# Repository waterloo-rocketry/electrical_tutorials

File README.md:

# electrical_tutorials
Hardware &amp; software used in electrical tutorials

Contents:
* pic_template.X: contains an empty MPLAB X project for use with the `picdev` board (see schematics in canhw). The project is set up with all the necessary files to get CAN communication up and running.
* 2019_PIC_CAN_dev_board: contains the reference schematics used in the 2019 electrical Kicad tutorials.
* 2020_keychain_PIC: contains the desing files for the 2020 KiCAD tutorials.

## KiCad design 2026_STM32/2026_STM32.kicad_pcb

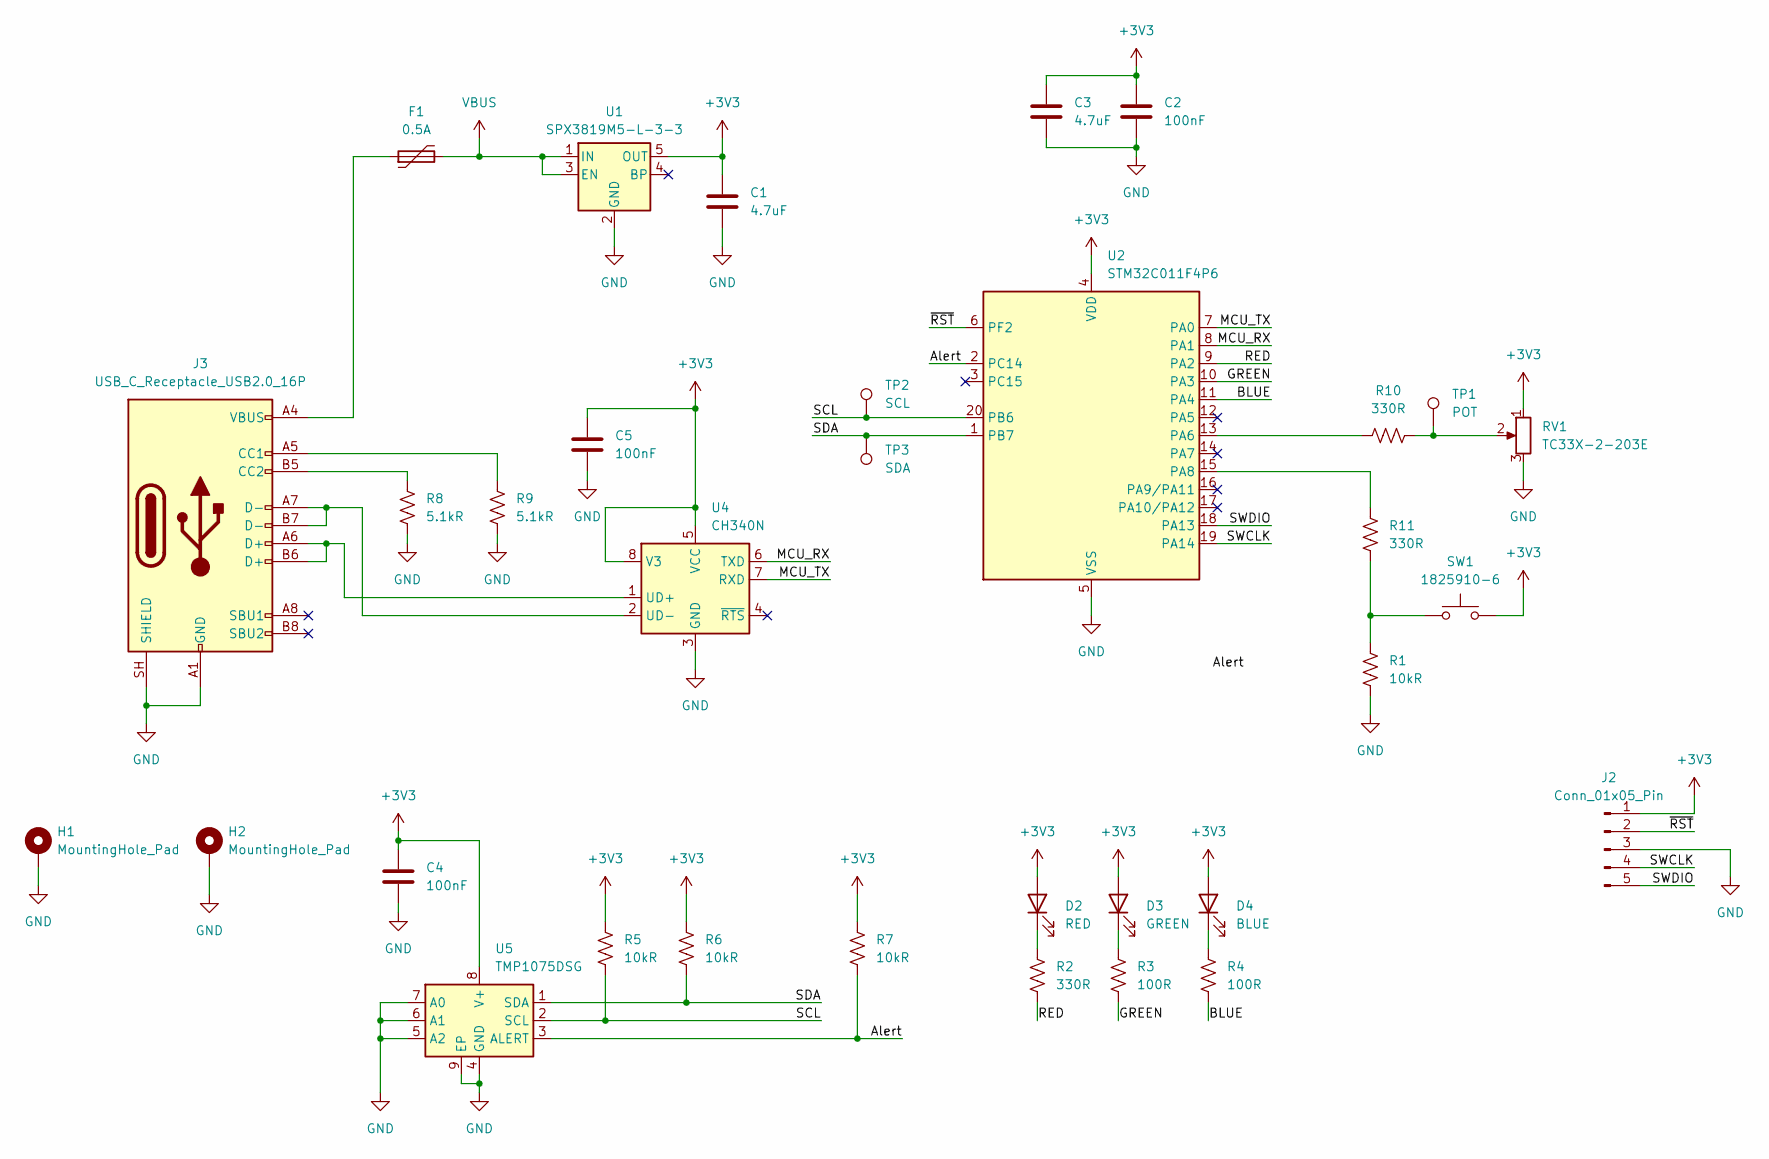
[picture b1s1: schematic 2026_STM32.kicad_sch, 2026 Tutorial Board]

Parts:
C1, C3: 4.7uF; C_0805_2012Metric_Pad1.18x1.45mm_HandSolder
C2, C4, C5: 100nF; C_0805_2012Metric_Pad1.18x1.45mm_HandSolder
D2: RED; D_1206_3216Metric_Pad1.42x1.75mm_HandSolder
D3: GREEN; D_1206_3216Metric_Pad1.42x1.75mm_HandSolder
D4: BLUE; D_1206_3216Metric_Pad1.42x1.75mm_HandSolder
F1: 0.5A; Fuse_0805_2012Metric_Pad1.15x1.40mm_HandSolder
H1, H2: MountingHole_Pad; MountingHole_3.2mm_M3_Pad
J2: Conn_01x05_Pin; PinHeader_1x05_P2.54mm_Vertical
J3: USB_C_Receptacle_USB2.0_16P; USB_C_Receptacle_GCT_USB4105-xx-A_16P_TopMnt_Horizontal; LCSC C165948
R1, R5, R6, R7: 10kR; C_0805_2012Metric_Pad1.18x1.45mm_HandSolder
R2, R10, R11: 330R; C_0805_2012Metric_Pad1.18x1.45mm_HandSolder
R3, R4: 100R; C_0805_2012Metric_Pad1.18x1.45mm_HandSolder
R8, R9: 5.1kR; C_0805_2012Metric_Pad1.18x1.45mm_HandSolder
RV1: TC33X-2-203E; PTV09A4015UB103
SW1: 1825910-6; SW_PUSH_6mm; LCSC C428628
TP1: POT; TestPoint_THTPad_D2.5mm_Drill1.2mm
TP2: SCL; TestPoint_THTPad_D2.5mm_Drill1.2mm
TP3: SDA; TestPoint_THTPad_D2.5mm_Drill1.2mm
U1: SPX3819M5-L-3-3; SOT-23-5
U2: STM32C011F4P6; TSSOP-20_4.4x6.5mm_P0.65mm; LCSC C7373263
U4: CH340N; JEITA_SOIC-8_3.9x4.9mm_P1.27mm
U5: TMP1075DSG; WSON-8-1EP_2x2mm_P0.5mm_EP0.9x1.6mm_ThermalVias

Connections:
+3V3: C1.1, C2.1, C3.1, C4.1, C5.1, D2.2 (A), D3.2 (A), D4.2 (A), J2.1, R5.1, R6.1, R7.1, RV1.1, SW1.2, U1.5 (OUT), U2.4 (VDD), U4.5 (VCC), U4.8 (V3), U5.8 (V+)
/Alert: R7.2, U2.2 (PC14), U5.3 (ALERT)
/BLUE: R4.2, U2.11 (PA4)
/GREEN: R3.2, U2.10 (PA3)
/MCU_RX: U2.8 (PA1), U4.6 (TXD)
/MCU_TX: U2.7 (PA0), U4.7 (RXD)
/RED: R2.2, U2.9 (PA2)
/SCL: R5.2, TP2.1 (1_1), U2.20 (PB6), U5.2 (SCL)
/SDA: R6.2, TP3.1 (1_1), U2.1 (PB7), U5.1 (SDA)
/SWCLK: J2.4, U2.19 (PA14)
/SWDIO: J2.5, U2.18 (PA13)
/~RST: J2.2, U2.6 (PF2)
GND: C1.2, C2.2, C3.2, C4.2, C5.2, H1.1 (1_1), H2.1 (1_1), J2.3, J3.A1 (GND), J3.A12 (GND), J3.B1 (GND), J3.B12 (GND), J3.SH (SHIELD), R1.2, R8.2, R9.2, RV1.3, U1.2 (GND), U2.5 (VSS), U4.3 (GND), U5.4 (GND), U5.5 (A2), U5.6 (A1), U5.7 (A0), U5.9 (EP)
unnamed: D2.1 (K), R2.1
unnamed: D3.1 (K), R3.1
unnamed: D4.1 (K), R4.1
unnamed: F1.1, J3.A4 (VBUS), J3.A9 (VBUS), J3.B4 (VBUS), J3.B9 (VBUS)
unnamed: J3.A5 (CC1), R9.1
unnamed: J3.B5 (CC2), R8.1
unnamed: R1.1, R11.1, SW1.1
unnamed: R10.2, RV1.2, TP1.1 (1_1)
unnamed: R10.1, U2.13 (PA6)
unnamed: R11.2, U2.15 (PA8)
unnamed: J3.A6 (D+), J3.B6 (D+), U4.1 (UD+)
unnamed: J3.A7 (D-), J3.B7 (D-), U4.2 (UD-)
VBUS: F1.2, U1.1 (IN), U1.3 (EN)

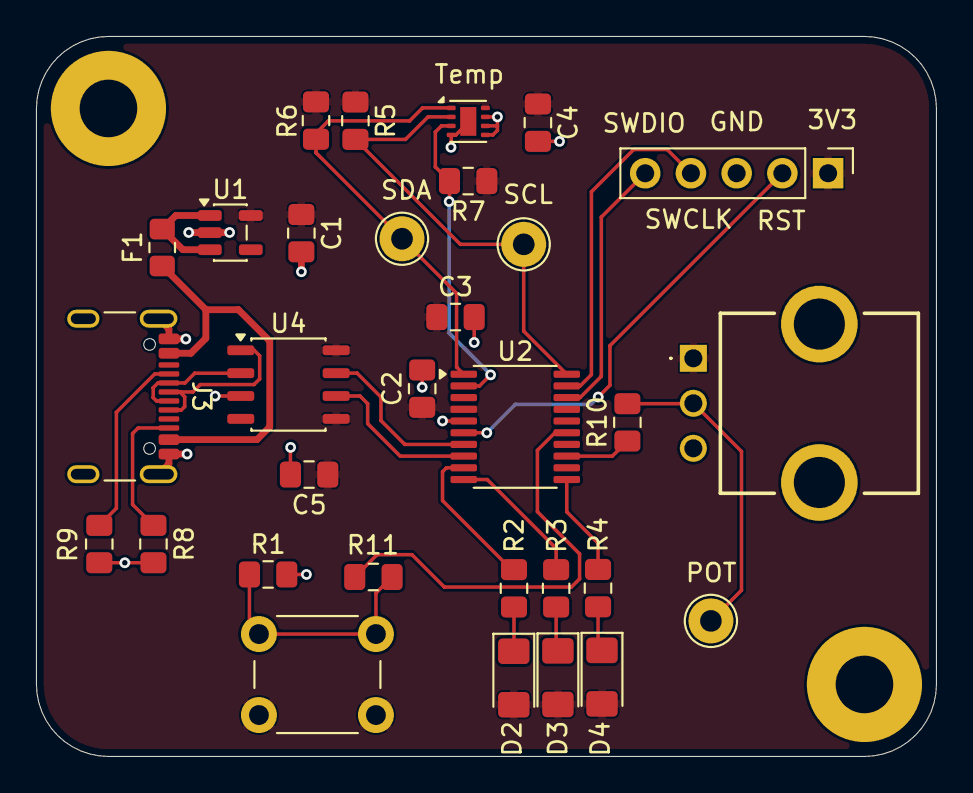
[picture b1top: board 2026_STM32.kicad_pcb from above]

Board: 2 copper layers, 50.0 x 40.0 mm, 33 parts (0 on the bottom side), 26 nets.

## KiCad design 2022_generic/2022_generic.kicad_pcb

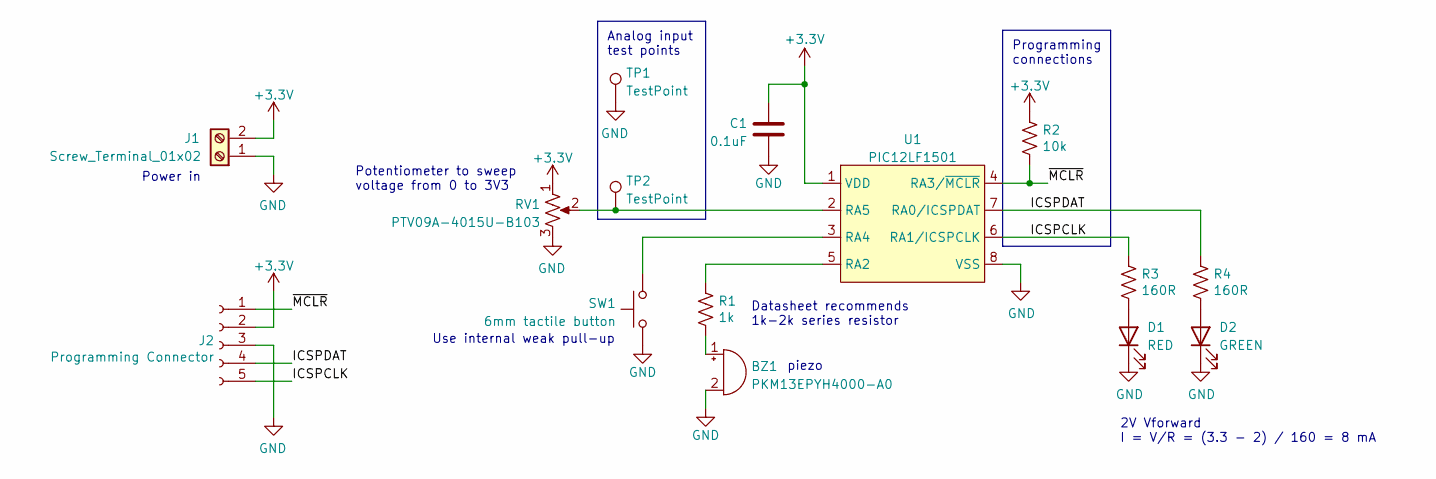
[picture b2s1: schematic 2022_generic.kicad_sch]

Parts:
BZ1: PKM13EPYH4000-A0; C_Radial_D12.5mm_H25.0mm_P5.00mm
C1: 0.1uF; C_0805_2012Metric_Pad1.18x1.45mm_HandSolder
D1: RED; LED_1206_3216Metric_Pad1.42x1.75mm_HandSolder
D2: GREEN; LED_1206_3216Metric_Pad1.42x1.75mm_HandSolder
J1: Screw_Terminal_01x02; TerminalBlock_Phoenix_PT-1,5-2-5.0-H_1x02_P5.00mm_Horizontal
J2: Programming Connector; PinHeader_5x2.54_SMD_90deg_952-3198-1-ND
R1: 1k; R_0805_2012Metric_Pad1.20x1.40mm_HandSolder
R2: 10k; R_0805_2012Metric_Pad1.20x1.40mm_HandSolder
R3, R4: 160R; R_0805_2012Metric_Pad1.20x1.40mm_HandSolder
RV1: PTV09A-4015U-B103; Potentiometer_Bourns_PTV09A-1_Single_Vertical
SW1: 6mm tactile button; SW_PUSH_6mm
TP1, TP2: TestPoint; TestPoint_THTPad_2.0x2.0mm_Drill1.0mm
U1: PIC12LF1501; SOIC-8_3.9x4.9mm_P1.27mm

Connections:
+3.3V: C1.2, J1.2, J2.2, R2.1, RV1.1, U1.1 (VDD)
/ICSPCLK: J2.5, R3.1, U1.6 (RA1/ICSPCLK)
/ICSPDAT: J2.4, R4.1, U1.7 (RA0/ICSPDAT)
/~MCLR: J2.1, R2.2, U1.4 (RA3/~MCLR)
GND: BZ1.2 (+), C1.1, D1.1 (K), D2.1 (K), J1.1, J2.3, RV1.3, SW1.2, TP1.1, U1.8 (VSS)
unnamed: BZ1.1 (-), R1.2
unnamed: D1.2 (A), R3.2
unnamed: D2.2 (A), R4.2
unnamed: R1.1, U1.5 (RA2)
unnamed: RV1.2, TP2.1, U1.2 (RA5)
unnamed: SW1.1, U1.3 (RA4)

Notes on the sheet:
Power in
Programming connections
2V Vforward I = V/R = (3.3 - 2) / 160 = 8 mA
Potentiometer to sweep voltage from 0 to 3V3
piezo
Datasheet recommends 1k-2k series resistor
Use internal weak pull-up
Analog input test points

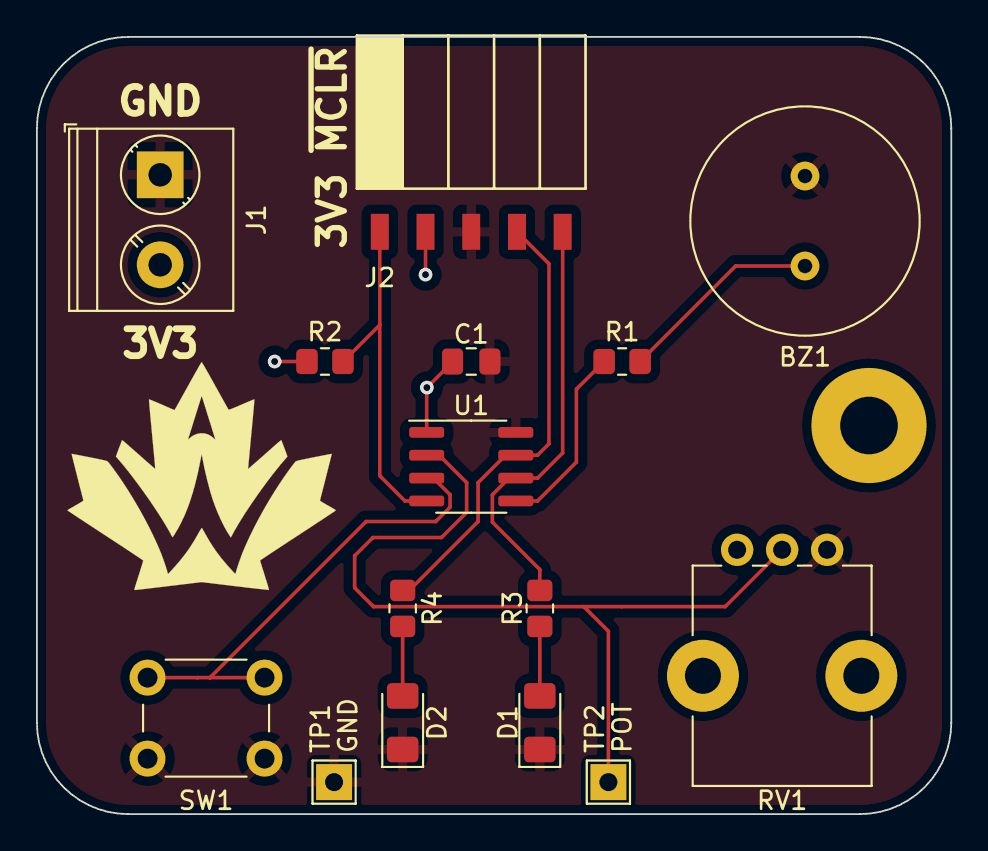
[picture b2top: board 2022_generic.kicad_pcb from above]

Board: 2 copper layers, 50.8 x 43.2 mm, 17 parts (1 on the bottom side), 11 nets.

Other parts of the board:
LOGO1: LOGO; Logo_SilkScreen_15mm
LOGO2: LOGO; Logo_Horizontal_Silkscreen_10mm

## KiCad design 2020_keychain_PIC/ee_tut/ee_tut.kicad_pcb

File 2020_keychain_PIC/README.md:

# Design Files for the 2020 Electrical Tutorials

## Steps:
1. Create new KICAD Project
2. Open schematic -> library editor, create a new library.
3. create a new symbol in that library
4. draw the symbol based on the datasheet (Using the L vaiant):
https://ww1.microchip.com/downloads/en/DeviceDoc/PIC16-L-F15313_23-Data-Sheet-40001897B.pdf
  1. place a rectangle, it is ok if the size isn't perfect, you can adjust it later
  2. hover over the edge of the rectangle and press e to edit the properties, select fill background
  3. place pins based on data sheet. it is best to place them grouped together by purpose, but in order like on the datasheet is good for this.
  4. If you need to move anything around you can hover over it and hit m to move it. To adjust the size of the rectangle you can use g for grab.
5. save the new symbol and exit the symbol editor
6. add the new PIC16LF15313 symbol to the shcematic
7. place the rest of the parts
8. add connections
9. anotate schematic

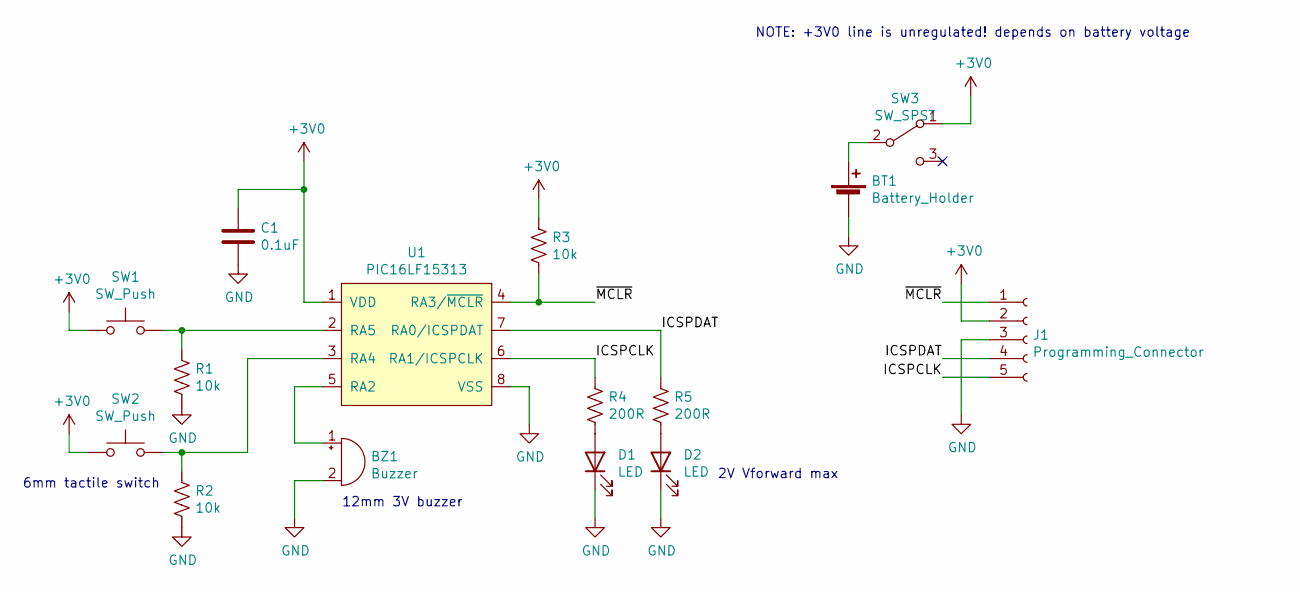
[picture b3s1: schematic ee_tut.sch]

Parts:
BT1: Battery_Holder; BatteryHolder_Keystone_3002_1x2032
BZ1: Buzzer; Buzzer_12x9.5RM7.6
C1: 0.1uF; C_0805_2012Metric_Pad1.15x1.40mm_HandSolder
D1, D2: LED; LED_1206_3216Metric_Pad1.42x1.75mm_HandSolder
J1: Programming_Connector; PinHeader_5x2.54_SMD_90deg_952-3198-1-ND
R1, R2, R3: 10k; R_0805_2012Metric_Pad1.15x1.40mm_HandSolder
R4, R5: 200R; R_0805_2012Metric_Pad1.15x1.40mm_HandSolder
SW1, SW2: SW_Push; SW_PUSH_6mm
SW3: SW_SPST; SW_E-Switch_EG1224_SPDT_Angled
U1: PIC16LF15313; SOIC-8_3.9x4.9mm_P1.27mm

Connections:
+3V0: C1.1, J1.2, R3.1, SW1.1, SW2.1, SW3.1 (A), U1.1 (VDD)
/ICSPCLK: J1.5, R4.1, U1.6 (RA1/ICSPCLK)
/ICSPDAT: J1.4, R5.1, U1.7 (RA0/ICSPDAT)
/~MCLR: J1.1, R3.2, U1.4 (RA3/~MCLR)
GND: BT1.2 (-), BZ1.2 (+), C1.2, D1.1 (K), D2.1 (K), J1.3, R1.2, R2.2, U1.8 (VSS)
unnamed: BT1.1 (+), SW3.2 (B)
unnamed: BZ1.1 (-), U1.5 (RA2)
unnamed: D1.2 (A), R4.2
unnamed: D2.2 (A), R5.2
unnamed: R1.1, SW1.2, U1.2 (RA5)
unnamed: R2.1, SW2.2, U1.3 (RA4)

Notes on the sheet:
12mm 3V buzzer
6mm tactile switch
2V Vforward max
NOTE: +3V0 line is unregulated! depends on battery voltage

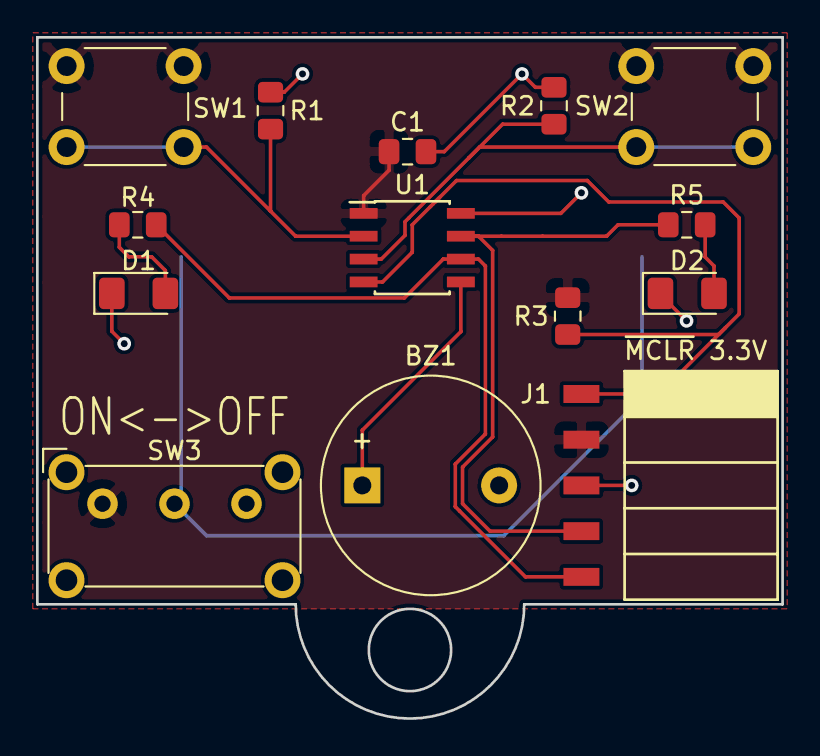
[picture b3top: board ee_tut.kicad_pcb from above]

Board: 2 copper layers, 41.4 x 37.8 mm, 15 parts (1 on the bottom side), 11 nets.

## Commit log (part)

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2019-09-20 Add initial reference schematic
2019-09-21 Add annotations
2019-10-26 Add PIC18F boilerplate for picdev
    This sets up a bare bones project for using with the picdev board.
    Canlib is included as a submodule.
2019-10-26 Add README
2019-10-28 Add tutorial schematic pdf
2019-11-01 Kill off the autogen Makefile
    It causes build issues when cloning the project and gets autogenerated anyway
2020-09-06 Create initial schematic for 2020 tutorial project.
2020-09-08 Finish initial board desing.
2020-09-13 Adress review comments :good_stuff:
2020-10-27 add demo code for keychain board.
2022-08-07 Add generic 2022 tutorial schematic and pcb
2022-08-08 Add mounting hole, move test points, generate pdf and gerbers
2022-08-08 Actually save PCB
2022-08-15 Add pot explanation and test point numbers
2022-09-16 Update PIC part number
2022-09-16 Add generic 2022 tutorial schematic and pcb (#2)
2024-09-03 2024 respin tutorial board first draft schematic
